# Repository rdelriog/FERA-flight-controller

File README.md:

# FERA — Modular Drone

One central unit, five vehicles. The FERA hub (flight controller, battery,
four identical ports) becomes a quadcopter, fixed-wing plane, rover, crawler or
boat by swapping the plug-in modules. An app detects what is attached, selects
the operation mode and runs the pre-flight checks.

| Area | Path | What |
|---|---|---|
| Interface standard | [`docs/port-spec.md`](docs/port-spec.md) | The FERA Port: mechanics, latch, pinout, module ID |
| Mechanical | [`cad/`](cad/) | Parametric CAD (Python / build123d) → STEP + 3MF |
| Electronics | [`hardware/fera-core/`](hardware/fera-core/) | FERA Core flight controller (KiCad 8, STM32H743) |
| Firmware | [`firmware/`](firmware/) | PX4 board port + `fera_modules`, ESP32 MAVLink bridge |
| App | [`app/`](app/) | FERA Configurator (React + TypeScript, WebSerial; Tauri desktop) |
| BOMs | [`bom/`](bom/) | Electronics and mechanical bills of materials |
| Simulation | [`sim/`](sim/) | PX4 SITL / Gazebo per mode |
| Legacy | [`legacy/`](legacy/), [`hardware/legacy/`](hardware/legacy/) | Mark I KiCad board, 2021 Altium board, F7 firmware stub |

## Baseline

- Firmware: PX4 (one binary, mode = airframe + parameter pack)
- Size class: 9-inch props (9047) on 2212 920 KV motors, 4S LiPo, 400 mm motor-to-motor diagonal
- MCU: STM32H743VIT6

## Quick start

```sh
# CAD: build all parts into cad/out/
python -m venv cad/.venv && cad/.venv/Scripts/pip install -r cad/requirements.txt
cad/.venv/Scripts/python cad/build.py

# App
cd app && npm install && npm run dev
```

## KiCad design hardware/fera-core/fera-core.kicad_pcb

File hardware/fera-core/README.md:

# FERA Core rev A — preliminary board and schematic

The flight controller and power distribution board that sits in the hub
between the four ports. **Preliminary design: for review, not for fabrication.**

| File | What |
|---|---|
| `fera-core.kicad_pro` | Open this in KiCad 8: schematic and board together |
| `fera-core.kicad_sch` + `mcu`, `sensors`, `power`, `io`, `ports` `.kicad_sch` | The schematic: an overview page and five pages. Generated — see below |
| `fera-core.kicad_pcb` | The board. Generated — see below |
| `fera.kicad_sym`, `fera.pretty/` | Project symbols (IMU, barometer, XT30) and the Kelvin shunt footprint |
| `pinmap.md` | MCU pin allocation, the reasoning behind it, and what was checked against datasheets |
| `audit.md` | Independent review of the circuit: every finding, what was fixed, what is still open |
| `gen/design.py` | **Source of truth**: parts, values, nets, placement, outline, copper, rules |
| `gen/make_schematic.py` | Writes the schematic from `design.py`; `--check` runs ERC and compares the netlist |
| `gen/build_board.py` | Builds the board from `design.py` with KiCad's Python API |
| `gen/router.py` | Small grid autorouter used for the preliminary routing |
| `gen/check_board.py` | KiCad DRC incl. schematic parity, signal length/impedance report, PDF plots |
| `gen/power_check.py` | Current calculation of the battery path on the board's real copper |
| `gen/mcu_pins.py`, `gen/ids.py` | STM32 pin table from KiCad's library; UUIDs shared by schematic and board |
| `plots/` | PDFs of the schematic and the layers, `power_density.png` |

## Regenerating

```sh
cd hardware/fera-core
KPY="C:/Program Files/KiCad/8.0/bin/python.exe"
VPY=../../cad/.venv/Scripts/python
python gen/make_schematic.py --check     # schematic + ERC + netlist comparison
$KPY gen/build_board.py --dump-pads      # placement check, pad geometry -> gen/pads.json
$VPY gen/escape_test.py                  # 10 s: is any pad walled in by the fixed copper?
$VPY gen/preview.py                      # route (10-15 min) -> gen/route_result.json, preview.png
$KPY gen/build_board.py --use-result     # tracks, vias, planes, pours, stack-up, net classes
python gen/check_board.py                # DRC, schematic parity, signal report, plots
$KPY gen/build_board.py --dump-copper    # filled copper -> gen/copper.json
$VPY gen/power_check.py                  # battery-path current calculation
python gen/make_bom.py                   # ../../bom/fera-core-revA.csv
```

`$VPY gen/preview.py --quick` routes only the plane vias and the frozen nets (1 s); that is
enough for `power_check.py` when only the power copper changed.

The schematic and the board are both overwritten on every run, so **make changes in
`gen/design.py`, not in KiCad**, until the design is taken over by hand. Once you start
editing in KiCad, stop regenerating. The footprints carry the UUIDs of their schematic
symbols, so KiCad's *Update PCB from Schematic* works on the files as they are.

## The schematic

Every pin has a short wire and a net label, and power pins have power symbols, so nets are
joined by name rather than by drawn wires. It is a complete, ERC-clean picture of the netlist,
not a hand-drawn schematic: fine for review and for driving the board, worth redrawing by
hand page by page later. Symbols come from KiCad's libraries wherever one exists
(STM32H743, INA226, LMR33630, TLV62569, LP5907, USBLC6, USB-C, microSD, Tag-Connect), which
lets `--check` compare every net against the library's pin names.

## What is on the board

- STM32H743VIT6, 16 MHz crystal, decoupling under the chip, SWD (Tag-Connect TC2030)
- ICM-42688-P IMU on SPI4, against the MCU corner that carries SPI4; DPS368 barometer;
  both on their own low-noise 3.3 V rail
- Battery input pads, 0.2 mΩ shunt with Kelvin sense pads + INA226, TVS clamp
- 5 V buck (LMR33630) for the ports' 5 V rail, with bulk capacitor and clamp
- System rail VSYS (5 V or USB through two diodes) feeding the 3.3 V buck (TLV62569), the
  sensor LDO and the GPS / TELEM / RC connectors, so USB cannot back-feed the battery side
- Four ports, each with a power connector and an 8-way signal connector, and per port: a
  TPS2069C current-limited switch for the module's 5 V (enable and fault to the MCU),
  100 Ω in series with S1–S3 and ID, 1 kΩ in the shared telemetry line and a USBLC6-4 clamp
  on the contact side. Port 3.3 V has its own current-limited LDO (3V3P)
- USB-C with ESD protection, microSD, GPS / TELEM1 / RC / latch-sense connectors
- Safety button, three status LEDs, test pads (BOOT0, debug UART, buzzer)

## Board shape

The outline is driven by the hub: a 56 mm central square between the four
socket blocks, four lobes in the hub's free corners, and a tongue that carries
the USB-C connector to the hub wall. `cad/build.py` checks that this outline
fits inside the printed hub and places the standoffs under the mounting holes.

## Stack-up (6 layers, 1.6 mm)

| Layer | Copper | Use |
|---|---|---|
| F.Cu | 1 oz | Components, signals, ground fill, battery pours |
| In1 | 2 oz | GND plane (carries the motor return current) |
| In2 | 2 oz | 3V3 fill, also carries slow signals (0.2 mm tracks, 0.2 mm gaps) |
| In3 | 2 oz | VBAT plane (battery current to the four ports) |
| In4 | 2 oz | 5V plane |
| B.Cu | 1 oz | Decoupling, signals, ground fill |

Nets with a plane are not routed pad to pad: each surface pad gets a short stub
and a via. The router may also put slow signals (GPIO, UARTs, I2C, port lines) on In2; the
fast and sensitive nets (USB, SD, IMU, crystal, buck nodes, current sense) stay on the outer
layers over a solid plane. Where In2 tracks fence off a piece of the 3V3 fill, the router
joins that piece's vias back with a short outer-layer track (`stitch_plane` in `router.py`). The dielectric thicknesses in the board file are a typical build
(0.11 mm prepreg under the outer layers); the fabricator's own stack-up replaces them.

## Status (measured on the generated files)

| Check | Result |
|---|---|
| Schematic ERC (KiCad 8) | 0 errors, 0 warnings |
| Schematic netlist vs `design.py` | 501 pin-to-net assignments, 0 differences |
| Independent circuit review | Done, see `audit.md`. Its error and most warnings are fixed, including port protection; still open: 5 V budget, reverse polarity, telemetry mux and some optional parts |
| MCU functions vs KiCad's STM32H743 pin table | 44 of 44 on a pin that offers them |
| Schematic ↔ board parity (KiCad DRC) | 0 issues |
| Placement | 132 parts + 4 mounting holes, no courtyard overlaps, all inside the outline |
| Routing | 202 of 202 signal connections; every plane pad has its via |
| Board DRC | 0 errors, 0 unconnected items; about 140 silkscreen warnings (cosmetic). The stock USB-C footprint's ground pads sit 0.19 mm from its locating holes: allowed for that footprint only in `fera-core.kicad_dru` (0.25 mm everywhere else); confirm the fab accepts it |

The router's result depends on routing order, so a different placement can leave a
connection open; it ends with a repair pass that moves only the tracks in the way, and
`check_board.py` reports anything left.

### Battery path (`gen/power_check.py`)

Path: BAT+ pad → pour on top, bottom and an island in the VBAT layer → 0.2 mΩ shunt →
via field → 2 oz VBAT plane → port "+" pads, and back through the 2 oz GND plane to the BAT−
pad. Copper at about 70 °C, outer-layer ground fills ignored (pessimistic).

| Load | Board copper + shunt | of which shunt | Drop, battery pads to worst port (+ and −) | Connector contacts (8 × 0.8 mΩ) |
|---|---|---|---|---|
| 4 × 15 A = 60 A (XT30 continuous rating) | 6.1 W | 0.7 W | 77 mV + 32 mV | 1.4 W |
| 4 × 30 A = 120 A (XT30 momentary rating) | 24 W | 2.9 W | 154 mV + 63 mV | 5.8 W |

Loss scales with the square of the current: about 0.7 W at a 20 A hover and 2.7 W at 40 A.
Where the 6.0 W goes at 60 A: VBAT plane 2.0 W, GND plane 1.6 W, top-layer copper next to
the shunt pads 1.3 W, shunt 0.7 W, vias 0.3 W. The hottest spots are the 1 oz copper at the
two shunt pads and the three large vias beside the shunt (up to 9 A each at 60 A, 18 A at
120 A); `plots/power_density.png` shows them. 60 A continuous in still air would run the
board roughly 50 K above ambient, so that figure needs airflow or a lower rating; the
120 A case is a few-seconds burst.

What the calculation changed: the first via field sat in the 11 × 11 mm neck where the
battery lobe joins the board and nearly cut every plane there (7.8 W at 60 A). The neck is
now a no-via area, BAT− and the via field sit either side of it, and the buck's output
vias moved out of it.

### Signals (`gen/check_board.py`)

0.15 mm tracks over the 0.11 mm prepreg are about 56 Ω single-ended; a 0.15/0.15 mm pair is
about 97 Ω (USB wants 90 Ω ± 15 %). Confirm with the fabricator's stack-up.

| Group | Longest | Spread | Notes |
|---|---|---|---|
| IMU SPI4 (≤ 24 MHz) | 21.5 mm | 17.7 mm (105 ps) | SCK and CS 3.8 mm with no vias; MISO now detours (21.5 mm, 4 vias). Still short for 24 MHz |
| USB full speed, MCU to ESD part | 42.6 mm | 0.1 mm (1 ps) | D+ 2 vias, D− 0. Not a coupled pair: fine for 12 Mbit/s, re-route with KiCad's pair router (net class `USB`) if you want it tidy |
| USB, ESD part to connector | 5.7 mm | 0.5 mm | Frozen before anything else is routed |
| microSD SDMMC1 (≤ 50 MHz) | 45.4 mm | 9.4 mm (56 ps) | Routed first, 2 vias per line (the previous run had a 114 mm SD_CMD detour) |
| Crystal | 5.1 mm | — | No vias; other nets are kept out of its area on the top layer |
| Current-sense pair | 8.6 mm | 0.1 mm | From the shunt's own sense pads |

All of these are electrically short for their edge rates as long as the GPIO slew rate is set
to medium, so none needs length tuning. Top-layer signals run over the GND plane;
bottom-layer signals run over the 5 V plane.

## Known gaps before this can be fabricated

- **Open audit findings** (`audit.md`): the 5 V regulator is 3 A for all four ports (each
  port is now limited to 1.7–2.5 A, but four together can still exceed 3 A), there is no
  reverse-polarity protection, and ESC telemetry from all ports shares one UART.
- **The schematic is generated, not drawn.** It matches the board by construction and by
  check, and the circuit has now had one independent review, but that review could not
  read the STM32H743 datasheet and nothing has been simulated or built.
- **Port current rating.** XT30PW-F is 15 A continuous / 30 A momentary per the Amass
  spec; `docs/port-spec.md` asks for 30 A continuous. Either the spec comes down or the
  connector goes up (XT60PW) after the Phase 1 tests. The port connectors here are
  placeholders in any case (XT30 + 2x4 1.27 mm header).
- **Battery path.** Numbers above. The 1 oz copper at the shunt pads is the weak point;
  filled via-in-pad or a wider shunt package would fix it. The shunt part number is not chosen.
- **Not checked against a datasheet drawing:** the DPS368 land pattern (pin-out is checked),
  and the XT30 polarity was read from the Amass drawing and KiCad's footprint, not from a
  part: check with a meter on the first connector.
- **Buck converters:** placed by the datasheet rules (input capacitor under VIN/PGND,
  inductor at SW, thermal vias) but not simulated. The 5 V buck has three of the four
  22 µF output capacitors TI's table lists and no separate 220 nF input capacitor.
- **System rail routing:** VSYS is a 0.4 mm track about 190 mm long linking three corners
  of the board; fine for the 1 A it carries, but it should become a pour or a wider track
  when the board is routed by hand.
- Left off deliberately: second IMU, FRAM, CAN, ESC-telemetry mux, buzzer driver,
  RGB LED driver.

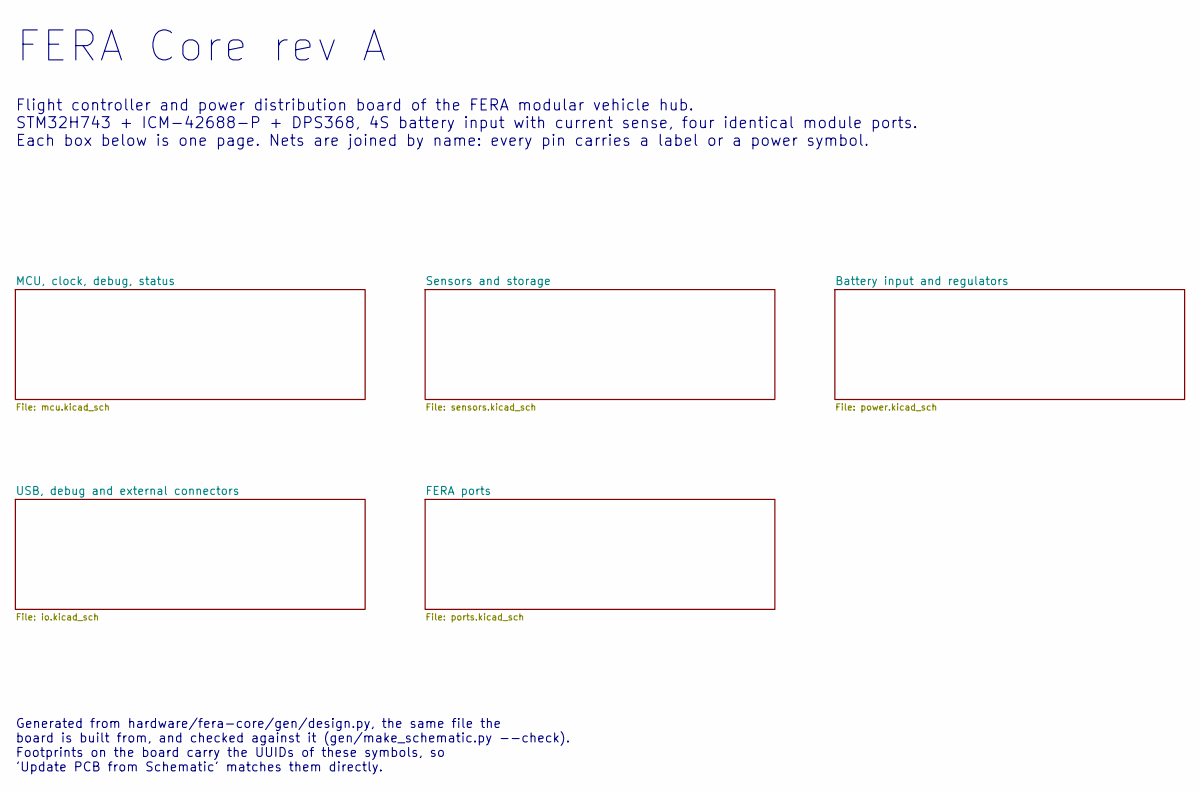
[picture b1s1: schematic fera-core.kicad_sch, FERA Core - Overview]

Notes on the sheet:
FERA Core rev A
Flight controller and power distribution board of the FERA modular vehicle hub. STM32H743 + ICM-42688-P + DPS368, 4S battery input with current sense, four identical module ports. Each box below is one page. Nets are joined by name: every pin carries a label or a power symbol.
Generated from hardware/fera-core/gen/design.py, the same file the board is built from, and checked against it (gen/make_schematic.py --check). Footprints on the board carry the UUIDs of these symbols, so 'Update PCB from Schematic' matches them directly.

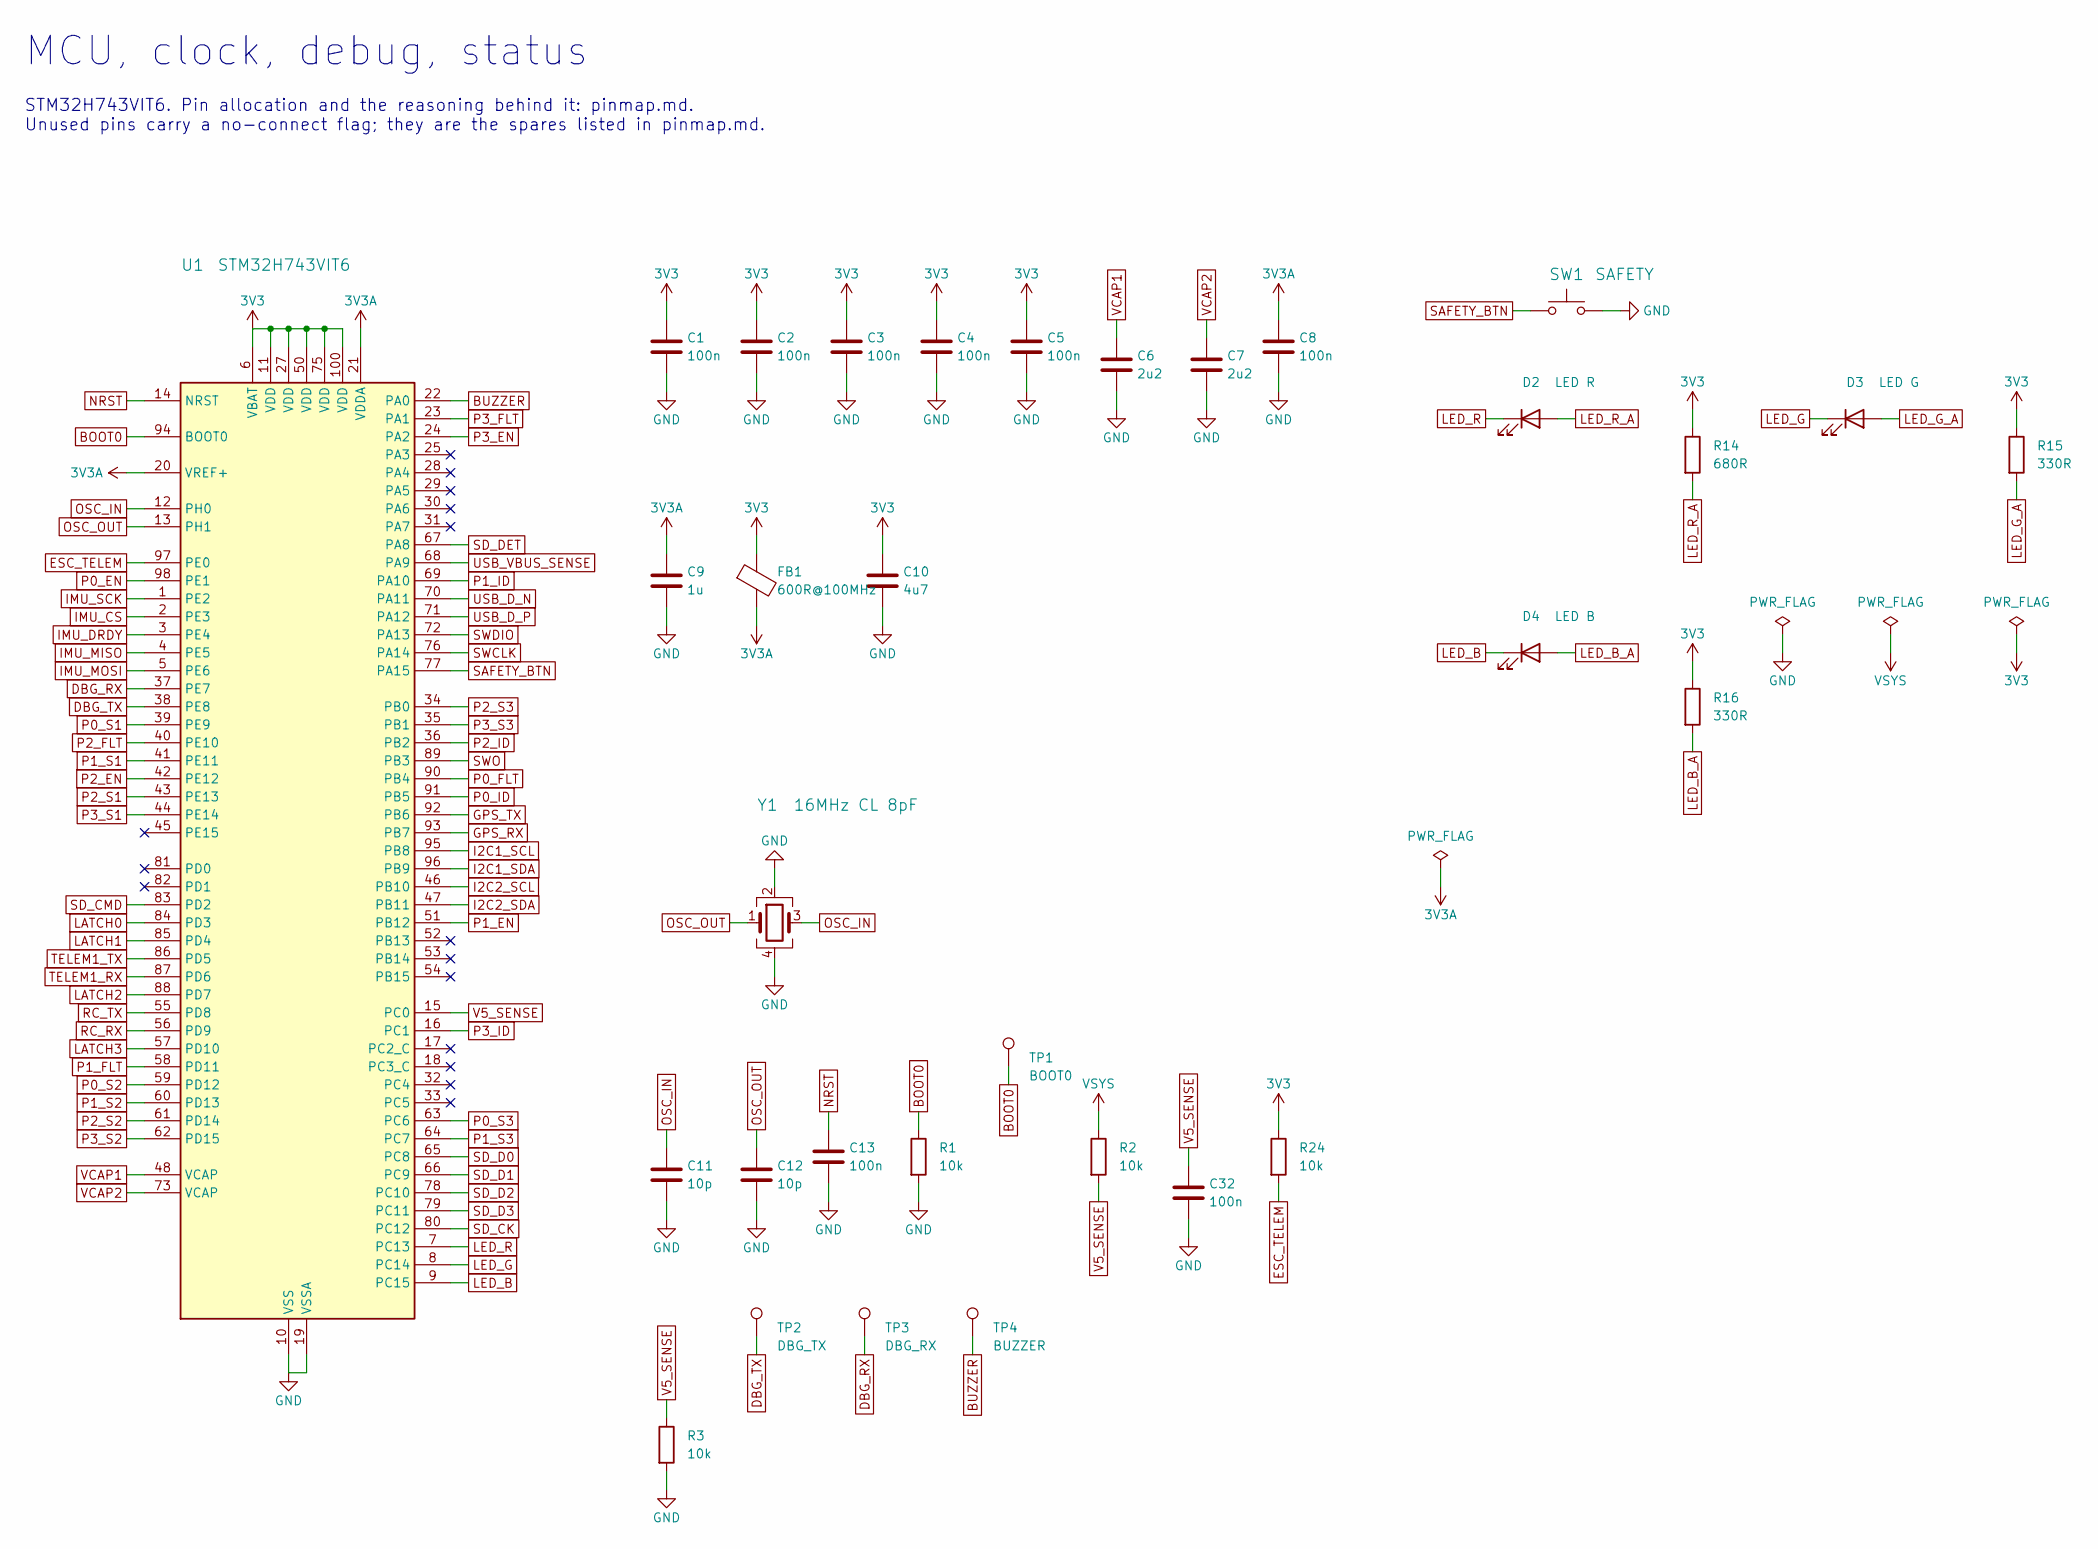
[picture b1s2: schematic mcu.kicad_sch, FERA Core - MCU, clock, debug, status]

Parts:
C1, C2, C3, C4, C5, C8, C13, C32: 100n; C_0402_1005Metric
C6, C7: 2u2; C_0603_1608Metric
C9: 1u; C_0402_1005Metric
C10: 4u7; C_0603_1608Metric
C11, C12: 10p; C_0402_1005Metric
D2: LED R; LED_0603_1608Metric
D3: LED G; LED_0603_1608Metric
D4: LED B; LED_0603_1608Metric
FB1: 600R@100MHz; L_0603_1608Metric
R1, R2, R3, R24: 10k; R_0402_1005Metric
R14: 680R; R_0402_1005Metric
R15, R16: 330R; R_0402_1005Metric
SW1: SAFETY; SW_SPST_B3U-1000P
TP1: BOOT0; TestPoint_Pad_D1.5mm
TP2: DBG_TX; TestPoint_Pad_D1.5mm
TP3: DBG_RX; TestPoint_Pad_D1.5mm
TP4: BUZZER; TestPoint_Pad_D1.5mm
U1: STM32H743VIT6; LQFP-100_14x14mm_P0.5mm
Y1: 16MHz CL 8pF; Crystal_SMD_3225-4Pin_3.2x2.5mm

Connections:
3V3: C1.1, C2.1, C3.1, C4.1, C5.1, C10.1, FB1.1, R14.1, R15.1, R16.1, R24.1, U1.6 (VBAT), U1.11 (VDD), U1.27 (VDD), U1.50 (VDD), U1.75 (VDD), U1.100 (VDD); also elsewhere on the board
3V3A: C8.1, C9.1, FB1.2, U1.20 (VREF+), U1.21 (VDDA)
BOOT0: R1.1, TP1.1, U1.94 (BOOT0)
BUZZER: TP4.1, U1.22 (PA0)
DBG_RX: TP3.1, U1.37 (PE7)
DBG_TX: TP2.1, U1.38 (PE8)
ESC_TELEM: R24.2, U1.97 (PE0); also elsewhere on the board
GND: C1.2, C2.2, C3.2, C4.2, C5.2, C6.2, C7.2, C8.2, C9.2, C10.2, C11.2, C12.2, C13.2, C32.2, R1.2, R3.2, SW1.2, U1.10 (VSS), U1.19 (VSSA), U1.26 (VSS), U1.49 (VSS), U1.74 (VSS), U1.99 (VSS), Y1.2, Y1.4; also elsewhere on the board
GPS_RX: U1.93 (PB7); also elsewhere on the board
GPS_TX: U1.92 (PB6); also elsewhere on the board
I2C1_SCL: U1.95 (PB8); also elsewhere on the board
I2C1_SDA: U1.96 (PB9); also elsewhere on the board
I2C2_SCL: U1.46 (PB10); also elsewhere on the board
I2C2_SDA: U1.47 (PB11); also elsewhere on the board
IMU_CS: U1.2 (PE3); also elsewhere on the board
IMU_DRDY: U1.3 (PE4); also elsewhere on the board
IMU_MISO: U1.4 (PE5); also elsewhere on the board
IMU_MOSI: U1.5 (PE6); also elsewhere on the board
IMU_SCK: U1.1 (PE2); also elsewhere on the board
LATCH0: U1.84 (PD3); also elsewhere on the board
LATCH1: U1.85 (PD4); also elsewhere on the board
LATCH2: U1.88 (PD7); also elsewhere on the board
LATCH3: U1.57 (PD10); also elsewhere on the board
LED_B: D4.1 (K), U1.9 (PC15)
LED_B_A: D4.2 (A), R16.2
LED_G: D3.1 (K), U1.8 (PC14)
LED_G_A: D3.2 (A), R15.2
LED_R: D2.1 (K), U1.7 (PC13)
LED_R_A: D2.2 (A), R14.2
NRST: C13.1, U1.14 (NRST); also elsewhere on the board
OSC_IN: C11.1, U1.12 (PH0), Y1.3
OSC_OUT: C12.1, U1.13 (PH1), Y1.1
P0_EN: U1.98 (PE1); also elsewhere on the board
P0_FLT: U1.90 (PB4); also elsewhere on the board
P0_ID: U1.91 (PB5); also elsewhere on the board
P0_S1: U1.39 (PE9); also elsewhere on the board
P0_S2: U1.59 (PD12); also elsewhere on the board
P0_S3: U1.63 (PC6); also elsewhere on the board
P1_EN: U1.51 (PB12); also elsewhere on the board
P1_FLT: U1.58 (PD11); also elsewhere on the board
P1_ID: U1.69 (PA10); also elsewhere on the board
P1_S1: U1.41 (PE11); also elsewhere on the board
P1_S2: U1.60 (PD13); also elsewhere on the board
P1_S3: U1.64 (PC7); also elsewhere on the board
P2_EN: U1.42 (PE12); also elsewhere on the board
P2_FLT: U1.40 (PE10); also elsewhere on the board
P2_ID: U1.36 (PB2); also elsewhere on the board
P2_S1: U1.43 (PE13); also elsewhere on the board
P2_S2: U1.61 (PD14); also elsewhere on the board
P2_S3: U1.34 (PB0); also elsewhere on the board
P3_EN: U1.24 (PA2); also elsewhere on the board
P3_FLT: U1.23 (PA1); also elsewhere on the board
P3_ID: U1.16 (PC1); also elsewhere on the board
P3_S1: U1.44 (PE14); also elsewhere on the board
P3_S2: U1.62 (PD15); also elsewhere on the board
P3_S3: U1.35 (PB1); also elsewhere on the board
RC_RX: U1.56 (PD9); also elsewhere on the board
RC_TX: U1.55 (PD8); also elsewhere on the board
SAFETY_BTN: SW1.1, U1.77 (PA15)
SD_CK: U1.80 (PC12); also elsewhere on the board
SD_CMD: U1.83 (PD2); also elsewhere on the board
SD_D0: U1.65 (PC8); also elsewhere on the board
SD_D1: U1.66 (PC9); also elsewhere on the board
SD_D2: U1.78 (PC10); also elsewhere on the board
SD_D3: U1.79 (PC11); also elsewhere on the board
SD_DET: U1.67 (PA8); also elsewhere on the board
SWCLK: U1.76 (PA14); also elsewhere on the board
SWDIO: U1.72 (PA13); also elsewhere on the board
SWO: U1.89 (PB3); also elsewhere on the board
TELEM1_RX: U1.87 (PD6); also elsewhere on the board
TELEM1_TX: U1.86 (PD5); also elsewhere on the board
USB_D_N: U1.70 (PA11); also elsewhere on the board
USB_D_P: U1.71 (PA12); also elsewhere on the board
USB_VBUS_SENSE: U1.68 (PA9); also elsewhere on the board
V5_SENSE: C32.1, R2.2, R3.1, U1.15 (PC0)
VCAP1: C6.1, U1.48 (VCAP)
VCAP2: C7.1, U1.73 (VCAP)
VSYS: R2.1; also elsewhere on the board

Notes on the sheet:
MCU, clock, debug, status
STM32H743VIT6. Pin allocation and the reasoning behind it: pinmap.md. Unused pins carry a no-connect flag; they are the spares listed in pinmap.md.

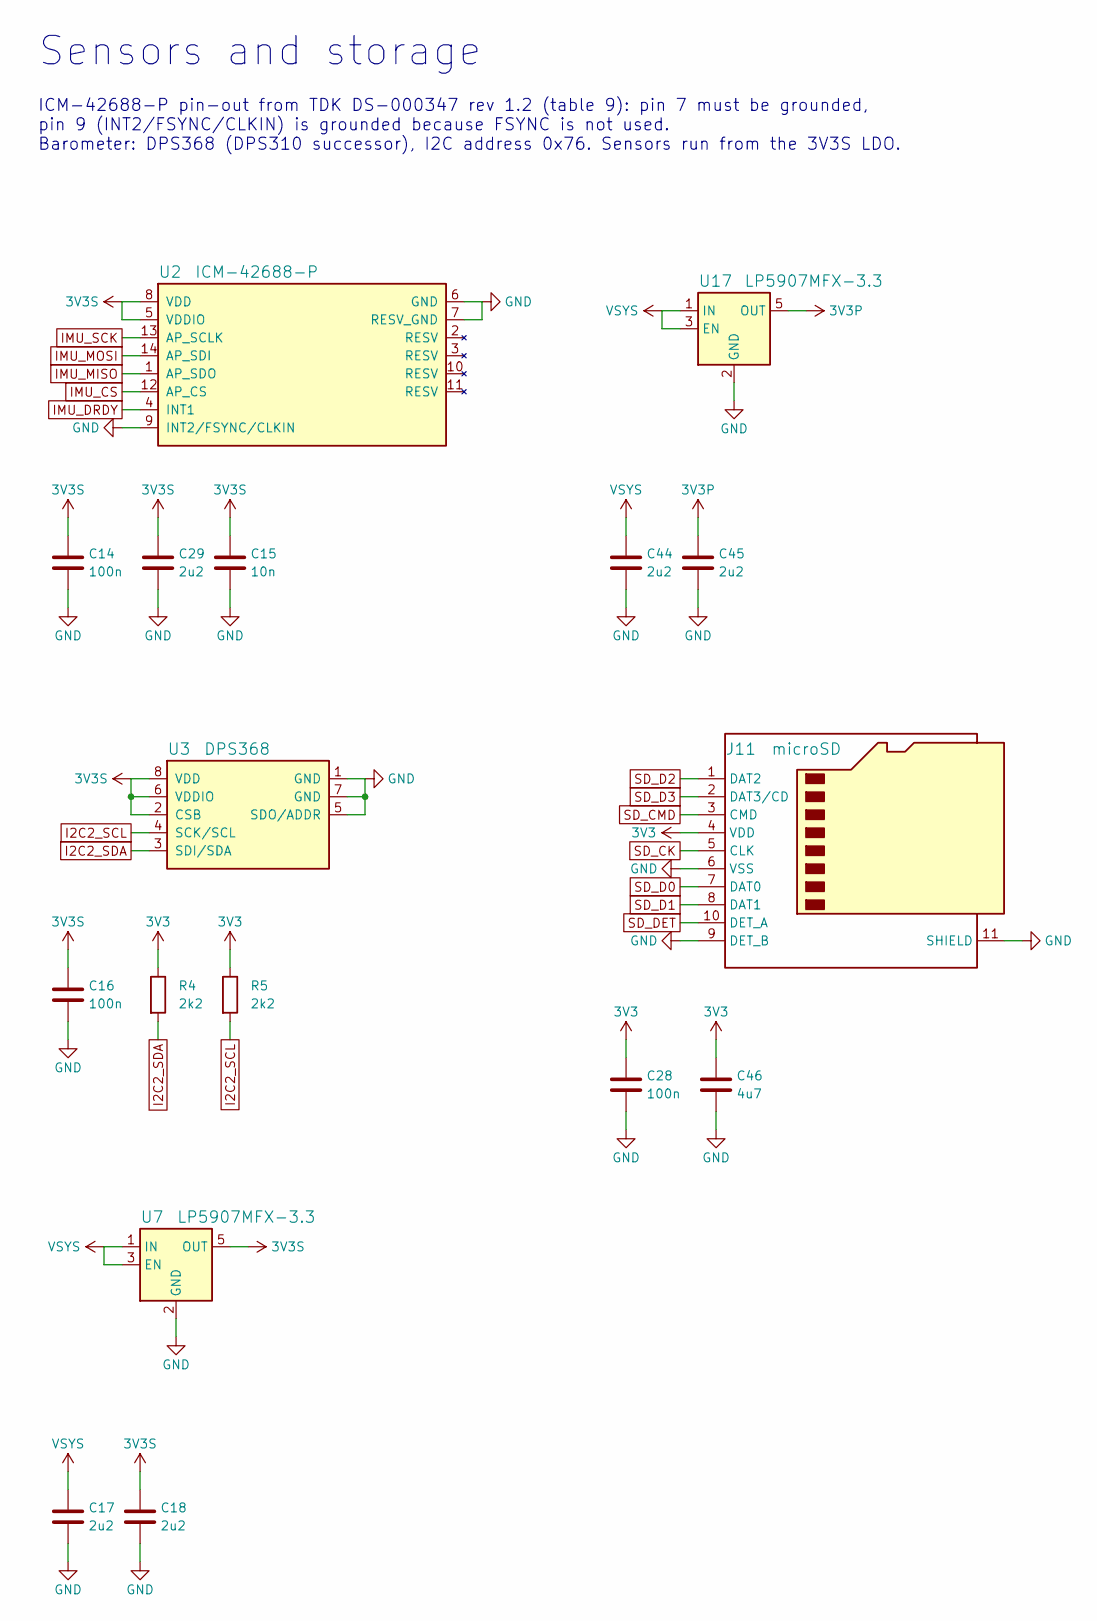
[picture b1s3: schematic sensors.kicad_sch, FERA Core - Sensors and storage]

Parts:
C14, C16, C28: 100n; C_0402_1005Metric
C15: 10n; C_0402_1005Metric
C17, C18, C29, C44, C45: 2u2; C_0402_1005Metric
C46: 4u7; C_0603_1608Metric
J11: microSD; microSD_HC_Hirose_DM3AT-SF-PEJM5
R4, R5: 2k2; R_0402_1005Metric
U2: ICM-42688-P; LGA-14_3x2.5mm_P0.5mm_LayoutBorder3x4y
U3: DPS368; Bosch_LGA-8_2x2.5mm_P0.65mm_ClockwisePinNumbering
U7, U17: LP5907MFX-3.3; SOT-23-5

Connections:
3V3: C28.1, C46.1, J11.4 (VDD), R4.1, R5.1; also elsewhere on the board
3V3P: C45.1, U17.5 (OUT); also elsewhere on the board
3V3S: C14.1, C15.1, C16.1, C18.1, C29.1, U2.5 (VDDIO), U2.8 (VDD), U3.2 (CSB), U3.6 (VDDIO), U3.8 (VDD), U7.5 (OUT)
GND: C14.2, C15.2, C16.2, C17.2, C18.2, C28.2, C29.2, C44.2, C45.2, C46.2, J11.6 (VSS), J11.9 (DET_B), J11.11 (SHIELD), U2.6 (GND), U2.7 (RESV_GND), U2.9 (INT2/FSYNC/CLKIN), U3.1 (GND), U3.5 (SDO/ADDR), U3.7 (GND), U7.2 (GND), U17.2 (GND); also elsewhere on the board
I2C2_SCL: R5.2, U3.4 (SCK/SCL); also elsewhere on the board
I2C2_SDA: R4.2, U3.3 (SDI/SDA); also elsewhere on the board
IMU_CS: U2.12 (AP_CS); also elsewhere on the board
IMU_DRDY: U2.4 (INT1); also elsewhere on the board
IMU_MISO: U2.1 (AP_SDO); also elsewhere on the board
IMU_MOSI: U2.14 (AP_SDI); also elsewhere on the board
IMU_SCK: U2.13 (AP_SCLK); also elsewhere on the board
SD_CK: J11.5 (CLK); also elsewhere on the board
SD_CMD: J11.3 (CMD); also elsewhere on the board
SD_D0: J11.7 (DAT0); also elsewhere on the board
SD_D1: J11.8 (DAT1); also elsewhere on the board
SD_D2: J11.1 (DAT2); also elsewhere on the board
SD_D3: J11.2 (DAT3/CD); also elsewhere on the board
SD_DET: J11.10 (DET_A); also elsewhere on the board
VSYS: C17.1, C44.1, U7.1 (IN), U7.3 (EN), U17.1 (IN), U17.3 (EN); also elsewhere on the board

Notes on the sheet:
Sensors and storage
ICM-42688-P pin-out from TDK DS-000347 rev 1.2 (table 9): pin 7 must be grounded, pin 9 (INT2/FSYNC/CLKIN) is grounded because FSYNC is not used. Barometer: DPS368 (DPS310 successor), I2C address 0x76. Sensors run from the 3V3S LDO.

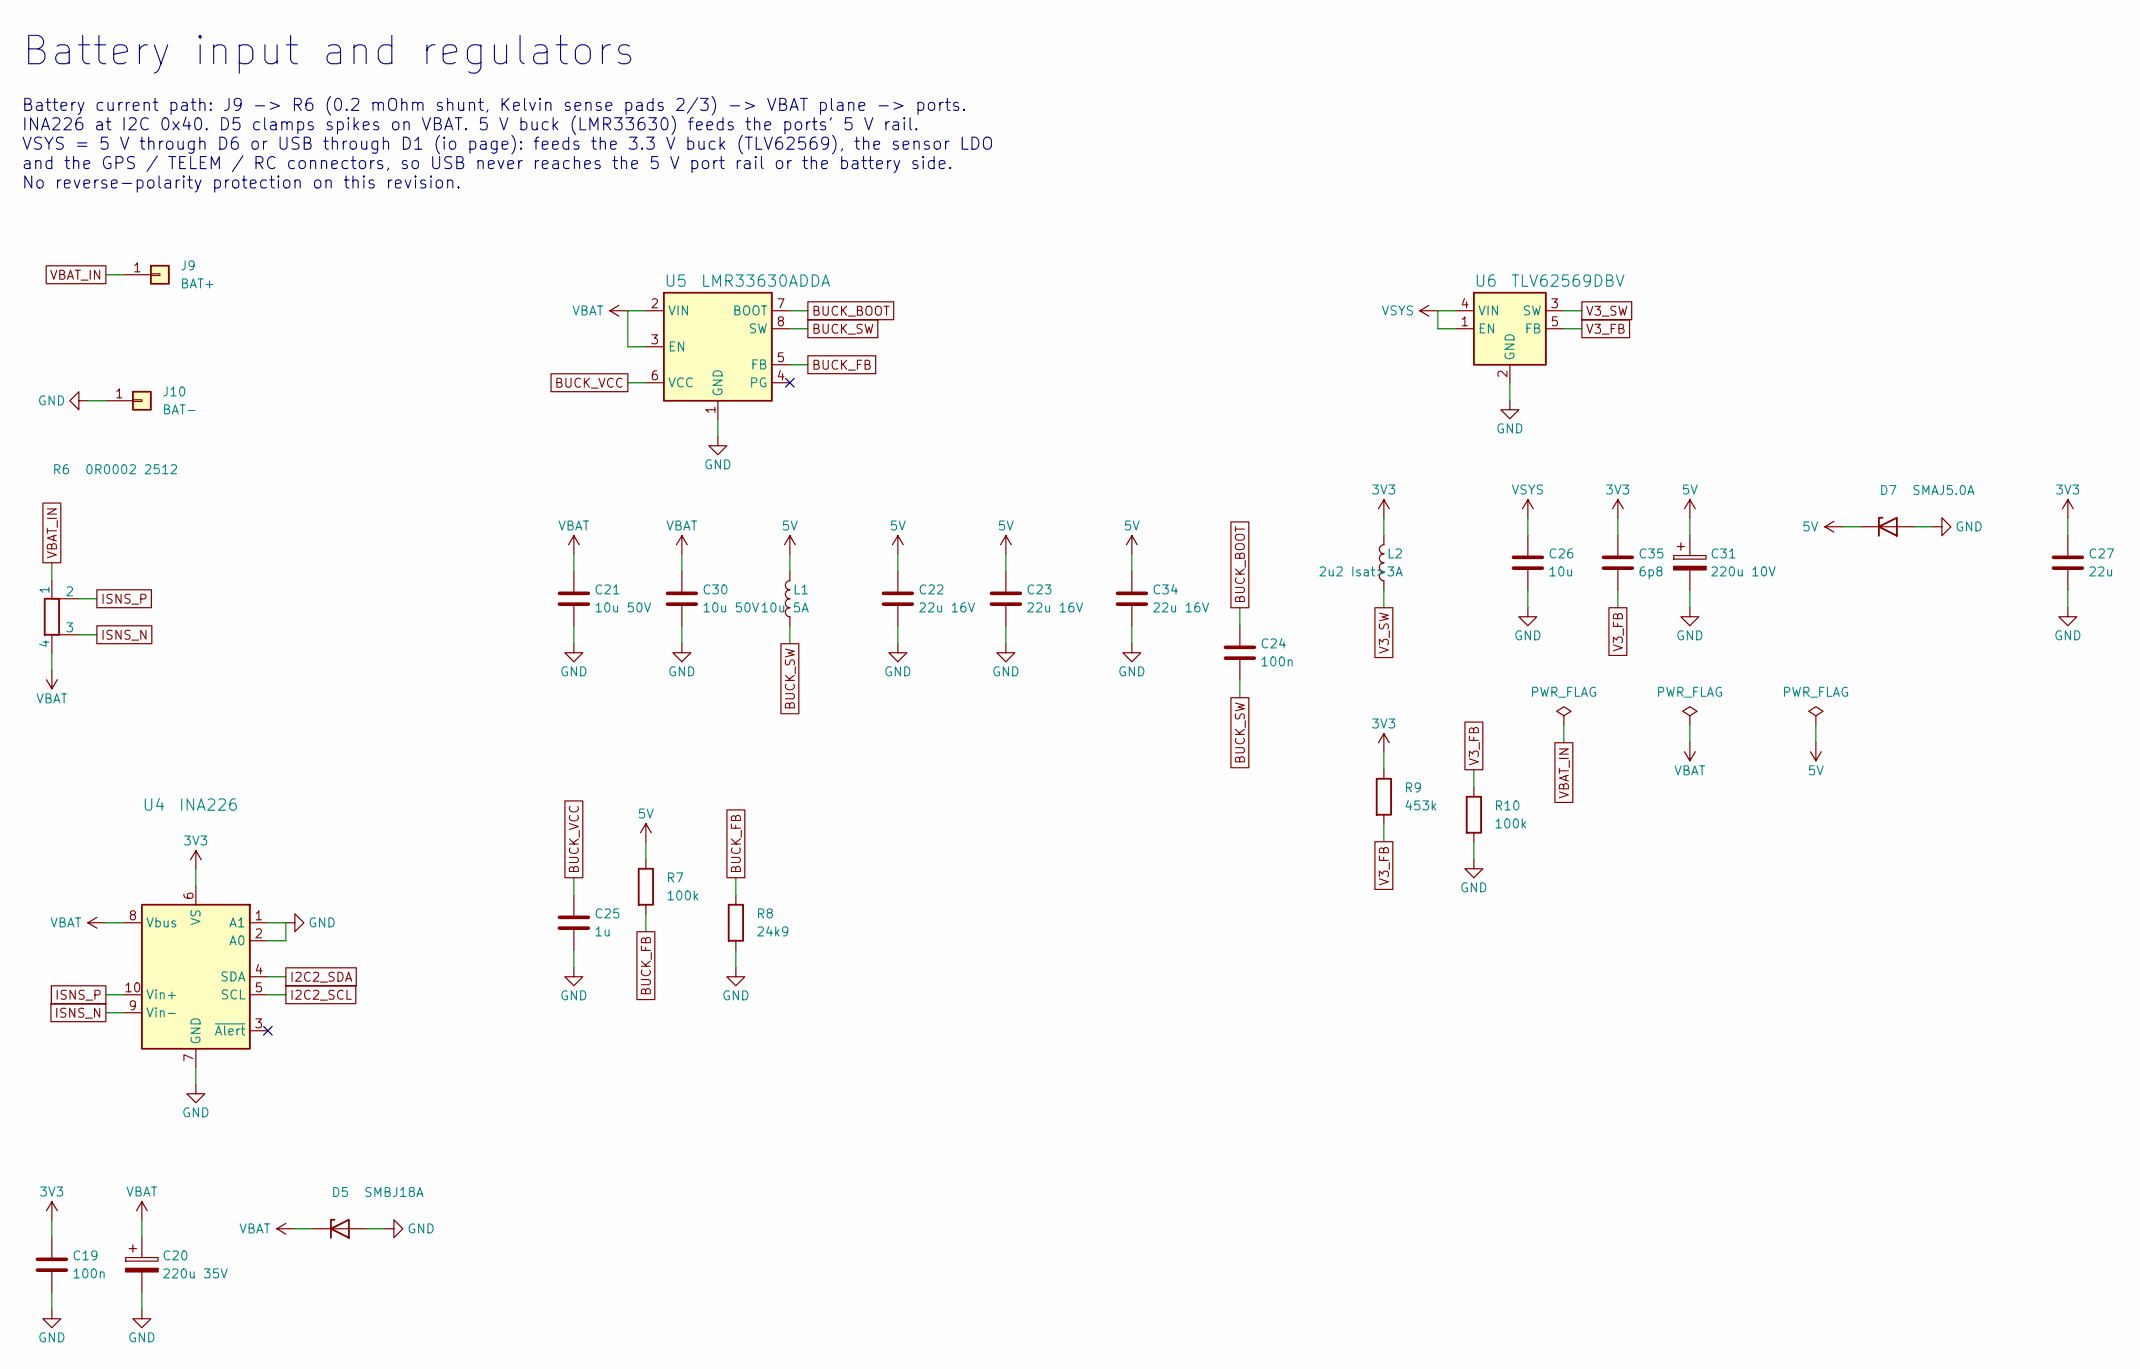
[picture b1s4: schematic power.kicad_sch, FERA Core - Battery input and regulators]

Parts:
C19, C24: 100n; C_0402_1005Metric
C20: 220u 35V; CP_Elec_6.3x7.7
C21: 10u 50V; C_1206_3216Metric
C22, C23, C34: 22u 16V; C_1210_3225Metric
C25: 1u; C_0402_1005Metric
C26: 10u; C_0805_2012Metric
C27: 22u; C_0805_2012Metric
C30: 10u 50V; C_0805_2012Metric
C31: 220u 10V; CP_Elec_6.3x7.7
C35: 6p8; C_0402_1005Metric
D5: SMBJ18A; D_SMB
D7: SMAJ5.0A; D_SMA
J9: BAT+; SolderWire-2.5sqmm_1x01_D2.4mm_OD3.6mm
J10: BAT-; SolderWire-2.5sqmm_1x01_D2.4mm_OD3.6mm
L1: 10u 5A; L_Bourns_SRP7028A_7.3x6.6mm
L2: 2u2 Isat>3A; L_Coilcraft_XAL4020-XXX
R6: 0R0002 2512; R_2512_Kelvin
R7, R10: 100k; R_0402_1005Metric
R8: 24k9; R_0402_1005Metric
R9: 453k; R_0402_1005Metric
U4: INA226; MSOP-10_3x3mm_P0.5mm
U5: LMR33630ADDA; HSOP-8-1EP_3.9x4.9mm_P1.27mm_EP2.41x3.1mm
U6: TLV62569DBV; SOT-23-5

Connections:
3V3: C19.1, C27.1, C35.1, L2.2, R9.1, U4.6 (VS); also elsewhere on the board
5V: C22.1, C23.1, C31.1, C34.1, D7.1 (K), L1.2, R7.1; also elsewhere on the board
BUCK_BOOT: C24.1, U5.7 (BOOT)
BUCK_FB: R7.2, R8.1, U5.5 (FB)
BUCK_SW: C24.2, L1.1, U5.8 (SW)
BUCK_VCC: C25.1, U5.6 (VCC)
GND: C19.2, C20.2, C21.2, C22.2, C23.2, C25.2, C26.2, C27.2, C30.2, C31.2, C34.2, D5.2 (A), D7.2 (A), J10.1, R8.2, R10.2, U4.1 (A1), U4.2 (A0), U4.7 (GND), U5.1 (GND), U5.9 (GND), U6.2 (GND); also elsewhere on the board
I2C2_SCL: U4.5 (SCL); also elsewhere on the board
I2C2_SDA: U4.4 (SDA); also elsewhere on the board
ISNS_N: R6.3, U4.9 (Vin-)
ISNS_P: R6.2, U4.10 (Vin+)
V3_FB: C35.2, R9.2, R10.1, U6.5 (FB)
V3_SW: L2.1, U6.3 (SW)
VBAT: C20.1, C21.1, C30.1, D5.1 (K), R6.4, U4.8 (Vbus), U5.2 (VIN), U5.3 (EN); also elsewhere on the board
VBAT_IN: J9.1, R6.1
VSYS: C26.1, U6.1 (EN), U6.4 (VIN); also elsewhere on the board

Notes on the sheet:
Battery input and regulators
Battery current path: J9 -> R6 (0.2 mOhm shunt, Kelvin sense pads 2/3) -> VBAT plane -> ports. INA226 at I2C 0x40. D5 clamps spikes on VBAT. 5 V buck (LMR33630) feeds the ports' 5 V rail. VSYS = 5 V through D6 or USB through D1 (io page): feeds the 3.3 V buck (TLV62569), the sensor LDO and the GPS 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

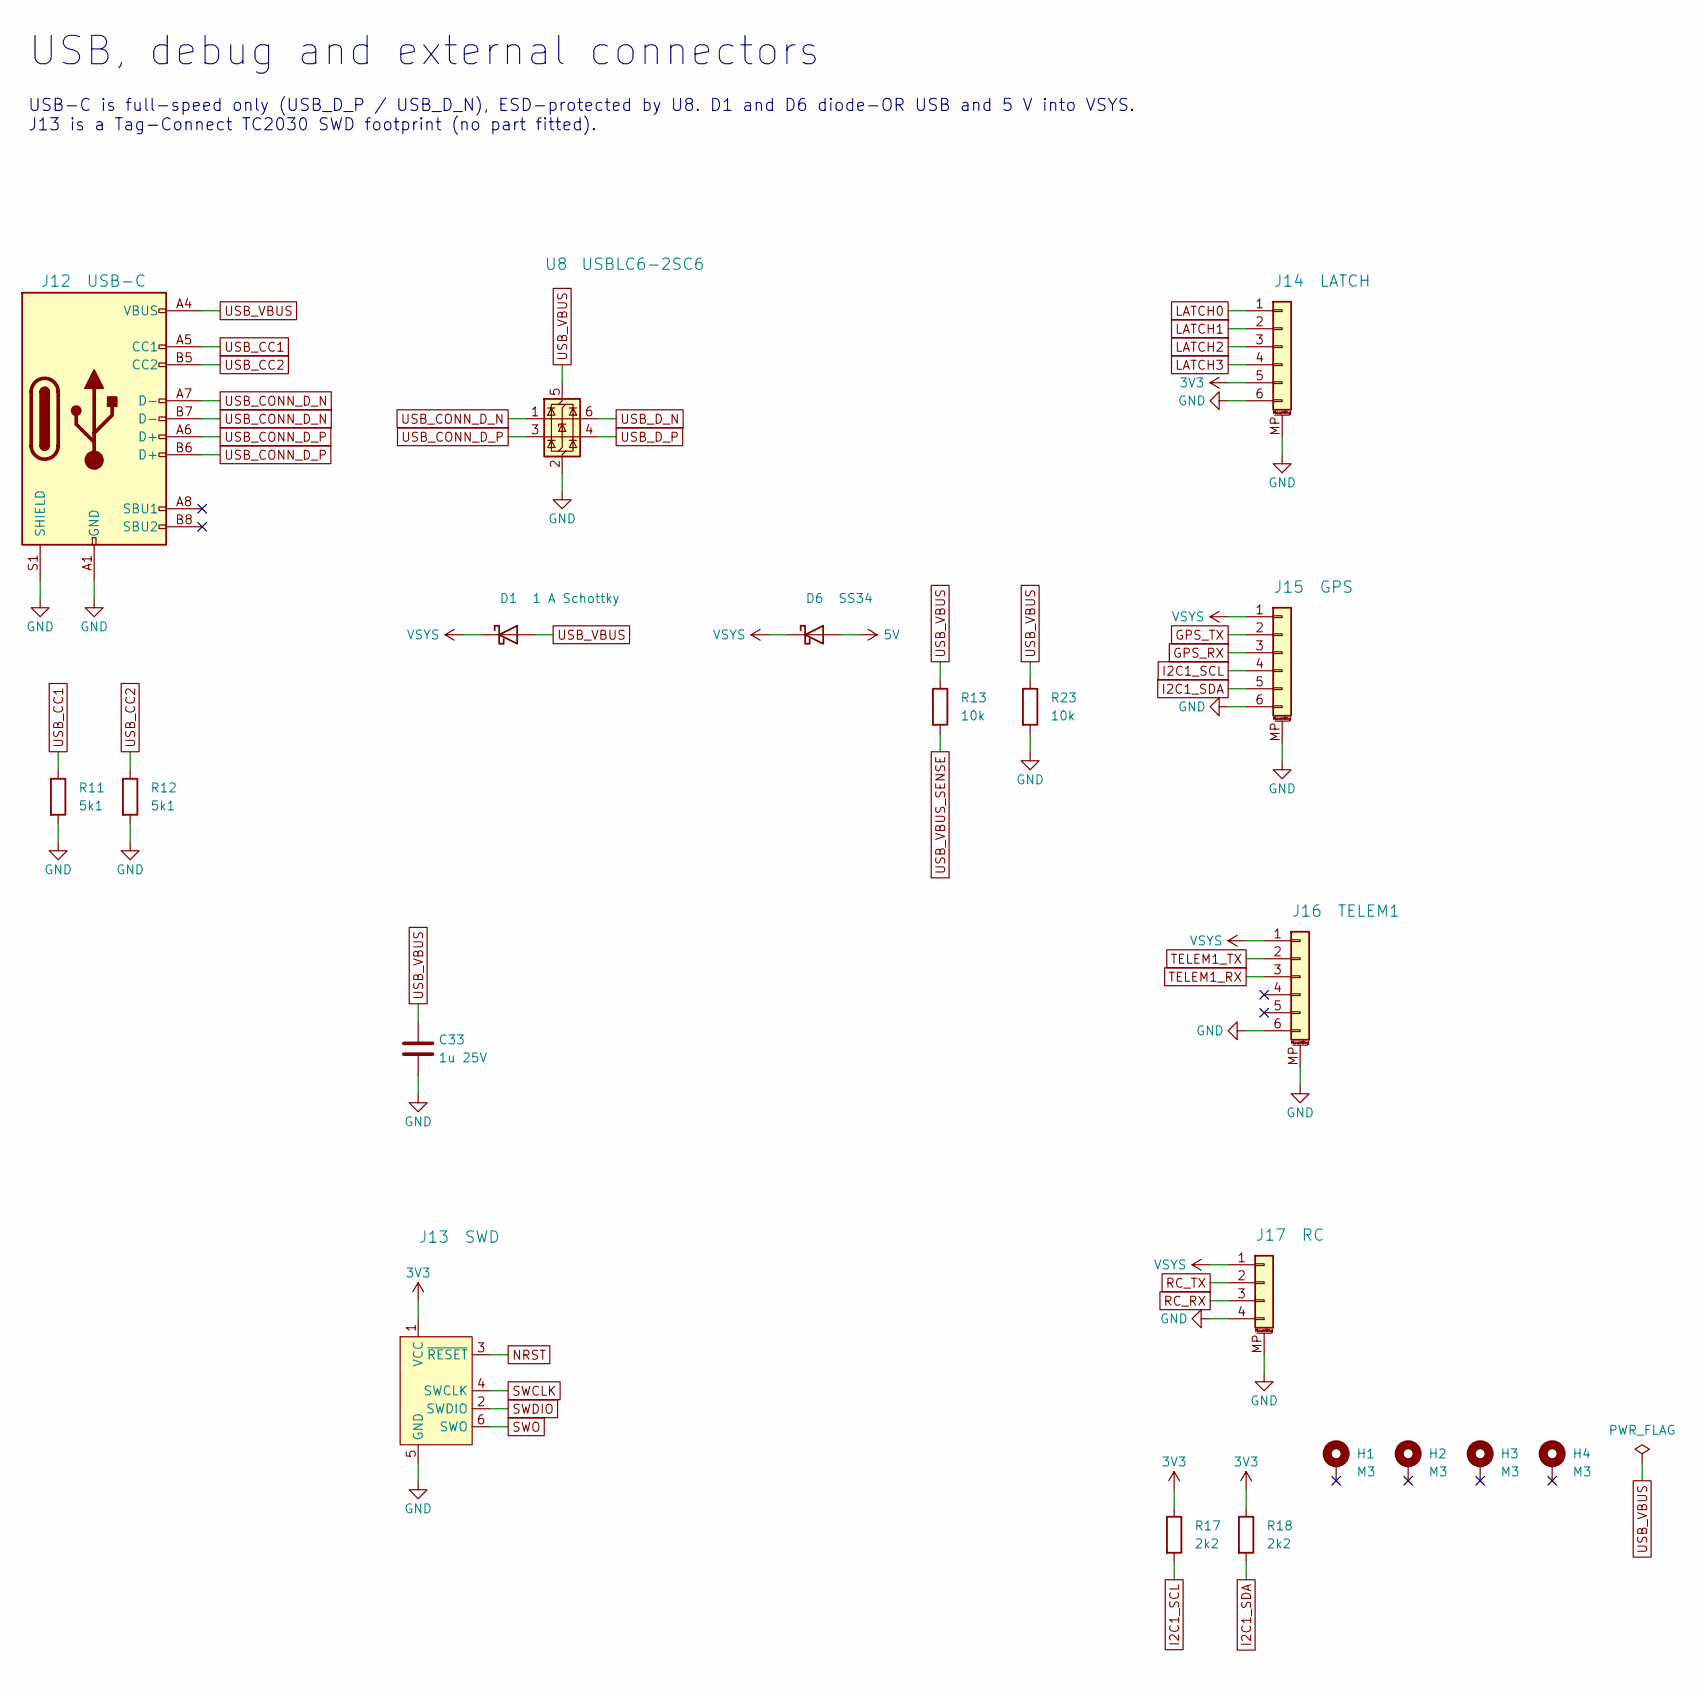
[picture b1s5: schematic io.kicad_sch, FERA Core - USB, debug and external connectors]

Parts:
C33: 1u 25V; C_0603_1608Metric
D1: 1 A Schottky; D_SOD-123
D6: SS34; D_SMA
H1, H2, H3, H4: M3; MountingHole_3.2mm_M3_Pad
J12: USB-C; USB_C_Receptacle_GCT_USB4105-xx-A_16P_TopMnt_Horizontal
J13: SWD; Tag-Connect_TC2030-IDC-NL_2x03_P1.27mm_Vertical
J14: LATCH; JST_GH_BM06B-GHS-TBT_1x06-1MP_P1.25mm_Vertical
J15: GPS; JST_GH_BM06B-GHS-TBT_1x06-1MP_P1.25mm_Vertical
J16: TELEM1; JST_GH_BM06B-GHS-TBT_1x06-1MP_P1.25mm_Vertical
J17: RC; JST_GH_BM04B-GHS-TBT_1x04-1MP_P1.25mm_Vertical
R11, R12: 5k1; R_0402_1005Metric
R13, R23: 10k; R_0402_1005Metric
R17, R18: 2k2; R_0402_1005Metric
U8: USBLC6-2SC6; SOT-23-6

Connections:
3V3: J13.1 (VCC), J14.5, R17.1, R18.1; also elsewhere on the board
5V: D6.2 (A); also elsewhere on the board
GND: C33.2, J12.A1 (GND), J12.A12 (GND), J12.B1 (GND), J12.B12 (GND), J12.S1 (SHIELD), J13.5 (GND), J14.6, J14.MP (MountPin), J15.6, J15.MP (MountPin), J16.6, J16.MP (MountPin), J17.4, J17.MP (MountPin), R11.2, R12.2, R23.2, U8.2 (GND); also elsewhere on the board
GPS_RX: J15.3; also elsewhere on the board
GPS_TX: J15.2; also elsewhere on the board
I2C1_SCL: J15.4, R17.2; also elsewhere on the board
I2C1_SDA: J15.5, R18.2; also elsewhere on the board
LATCH0: J14.1; also elsewhere on the board
LATCH1: J14.2; also elsewhere on the board
LATCH2: J14.3; also elsewhere on the board
LATCH3: J14.4; also elsewhere on the board
NRST: J13.3 (~RESET); also elsewhere on the board
RC_RX: J17.3; also elsewhere on the board
RC_TX: J17.2; also elsewhere on the board
SWCLK: J13.4 (SWCLK); also elsewhere on the board
SWDIO: J13.2 (SWDIO); also elsewhere on the board
SWO: J13.6 (SWO); also elsewhere on the board
TELEM1_RX: J16.3; also elsewhere on the board
TELEM1_TX: J16.2; also elsewhere on the board
USB_CC1: J12.A5 (CC1), R11.1
USB_CC2: J12.B5 (CC2), R12.1
USB_CONN_D_N: J12.A7 (D-), J12.B7 (D-), U8.1 (I/O1)
USB_CONN_D_P: J12.A6 (D+), J12.B6 (D+), U8.3 (I/O2)
USB_D_N: U8.6 (I/O1); also elsewhere on the board
USB_D_P: U8.4 (I/O2); also elsewhere on the board
USB_VBUS: C33.1, D1.2 (A), J12.A4 (VBUS), J12.A9 (VBUS), J12.B4 (VBUS), J12.B9 (VBUS), R13.1, R23.1, U8.5 (VBUS)
USB_VBUS_SENSE: R13.2; also elsewhere on the board
VSYS: D1.1 (K), D6.1 (K), J15.1, J16.1, J17.1; also elsewhere on the board

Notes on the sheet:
USB, debug and external connectors
USB-C is full-speed only (USB_D_P / USB_D_N), ESD-protected by U8. D1 and D6 diode-OR USB and 5 V into VSYS. J13 is a Tag-Connect TC2030 SWD footprint (no part fitted).
